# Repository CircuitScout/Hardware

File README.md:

# Hardware
Hardware of CircuitScout

- The PCBPR_Main_control_V1 is the main control board design;
- The StepperMotor_module_V2_XIAO_RP2040_w_PWR is the Coral module design;

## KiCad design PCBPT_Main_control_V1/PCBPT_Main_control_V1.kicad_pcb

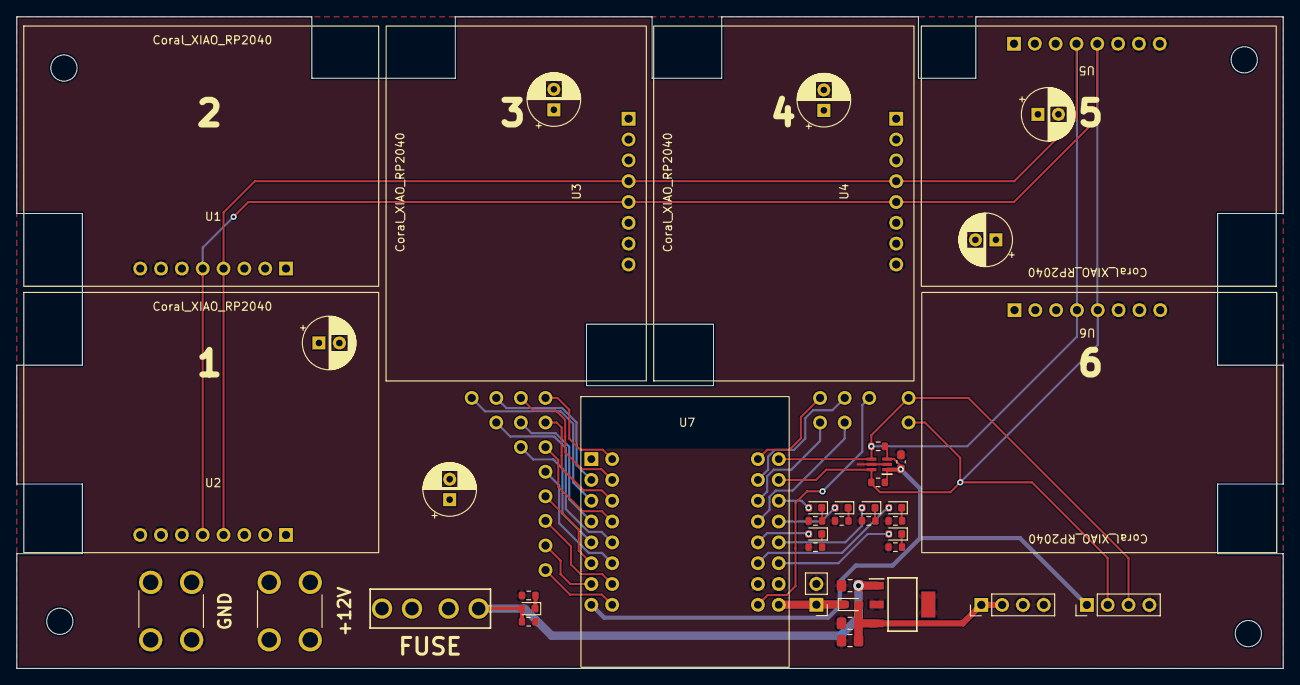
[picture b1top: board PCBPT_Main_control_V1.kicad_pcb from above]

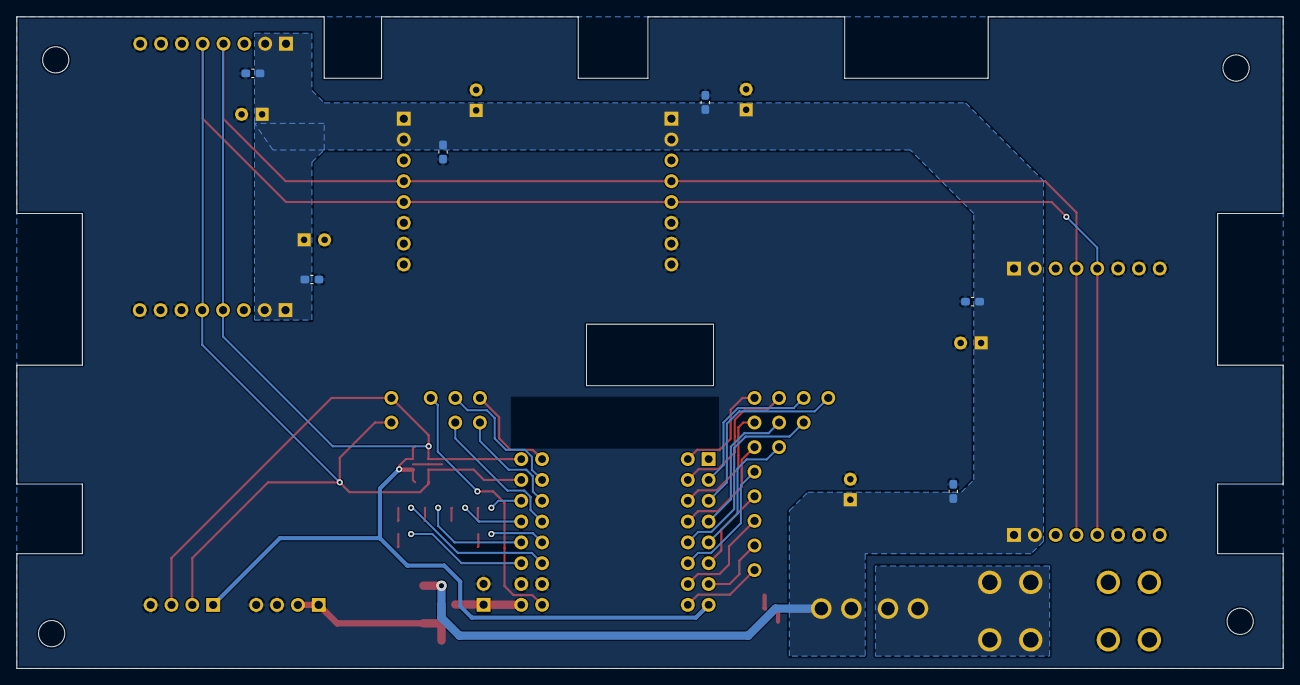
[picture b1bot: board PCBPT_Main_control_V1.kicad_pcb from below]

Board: 2 copper layers, 154.5 x 79.5 mm, 74 parts (6 on the bottom side), 40 nets.

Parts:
C1, C2, C3, C4, C5, C7: 0.1uF; C_0603_1608Metric_Pad1.08x0.95mm_HandSolder
C6: 0.01uF; C_0603_1608Metric_Pad1.08x0.95mm_HandSolder
C8, C9, C10, C11, C12, C13: 100uF; CP_Radial_D6.3mm_P2.50mm
C15: 0.47uF; C_0805_2012Metric_Pad1.18x1.45mm_HandSolder
C16: 22uF; C_0805_2012Metric_Pad1.18x1.45mm_HandSolder
C17: 0.1uF; C_0805_2012Metric_Pad1.18x1.45mm_HandSolder
D1, D2, D3, D4, D5, D6, D7: LED_Small_Filled; LED_0603_1608Metric
D8: Schottky; D_0603_1608Metric_Pad1.05x0.95mm_HandSolder
H1, H2, H3, H4: MountingHole; MountingHole_3.2mm_M3_DIN965
IC1: LM2940IMP-5.0_NOPB; SOT230P700X180-4N
IC2: LTC4311CSC6#TRPBF; SOT65P210X100-6N
J1: Fan; PinHeader_1x02_P2.54mm_Vertical
J2, J3: 8191-SEMS; 8191SEMS
J4, J8: Conn_01x04_Pin; PinHeader_1x04_P2.54mm_Vertical
R1, R2, R3, R4, R5, R6, R7, R8, R9: 10k; R_0603_1608Metric
R10: 499K; R_0603_1608Metric
TP1, TP2, TP3, TP4, TP5, TP6, TP7, TP8, TP11, TP12, TP13, TP14, TP15, TP16, TP17, TP18, TP19, TP20, TP21, TP22, TP23: TestPoint; 1_pin_sig
U1, U2, U3, U4, U5, U6: XIAO_RP2040_STEPPER_MODULE; Coral_XIAO_RP2040_stepper_ctrl
U7: Wemos/Lolin S2 mini; wemos S2 mini
U8: 3544-2

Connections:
+5V: D8.1 (K), J1.1, U7.9 (VBUS)
+12V: J2.1, J2.2, J2.3, J2.4, U8.1, U8.2
/ESP32S2_module/IND1: D2.2 (A), U7.28 (IO21)
/ESP32S2_module/IND2: D5.2 (A), U7.14 (IO35)
/ESP32S2_module/IND3: D3.2 (A), U7.13 (IO33)
/ESP32S2_module/IND4: D6.2 (A), U7.12 (IO18)
/ESP32S2_module/IND5: D4.2 (A), U7.27 (IO17)
/ESP32S2_module/IND6: D7.2 (A), U7.11 (IO16)
GND: C1.2, C2.2, C3.2, C4.2, C5.2, C6.2, C7.2, C8.2, C9.2, C10.2, C11.2, C12.2, C13.2, C15.2, C16.2, C17.2, IC1.2 (GND_1), IC1.4 (GND_2), IC2.2 (GND_1), IC2.5 (GND_2), J1.2, J3.1, J3.2, J3.3, J3.4, J4.3, J4.4, J8.4, R1.2, R2.2, R3.2, R4.2, R5.2, R6.2, R7.2, R10.1, U1.6 (GND), U1.7 (GND), U1.8 (GND), U2.6 (GND), U2.7 (GND), U2.8 (GND), U3.6 (GND), U3.7 (GND), U3.8 (GND), U4.6 (GND), U4.7 (GND), U4.8 (GND), U5.6 (GND), U5.7 (GND), U5.8 (GND), U6.6 (GND), U6.7 (GND), U6.8 (GND), U7.10 (GND), U7.26 (GND)
unnamed: D1.1 (K), R1.1
unnamed: D2.1 (K), R2.1
unnamed: D3.1 (K), R3.1
unnamed: D4.1 (K), R4.1
unnamed: D5.1 (K), R5.1
unnamed: D6.1 (K), R6.1
unnamed: D7.1 (K), R7.1
unnamed: TP1.1, U7.17 (IO1)
unnamed: TP6.1, U7.18 (IO2)
unnamed: TP11.1, U7.2 (IO3)
unnamed: TP12.1, U7.19 (IO4)
unnamed: TP16.1, U7.3 (IO5)
unnamed: TP3.1, U7.20 (IO6)
unnamed: TP5.1, U7.4 (IO7)
unnamed: TP18.1, U7.21 (IO8)
unnamed: TP17.1, U7.5 (IO9)
unnamed: TP15.1, U7.22 (IO10)
unnamed: TP13.1, U7.6 (IO11)
unnamed: TP4.1, U7.7 (IO12)
unnamed: TP2.1, U7.23 (IO13)
unnamed: TP14.1, U7.24 (IO14)
unnamed: TP19.1, U7.25 (IO15)
unnamed: TP20.1, U7.29 (IO34)
unnamed: TP22.1, U7.30 (IO36)
unnamed: TP23.1, U7.31 (IO38)
unnamed: TP21.1, U7.32 (IO40)
SCL: IC2.4 (BUS2), J8.3, R9.1, TP8.1, U1.4 (SCL), U2.4 (SCL), U3.4 (SCL), U4.4 (SCL), U5.4 (SCL), U6.4 (SCL), U7.16 (IO39)
SDA: IC2.6 (BUS1), J8.2, R8.1, TP7.1, U1.5 (SDA), U2.5 (SDA), U3.5 (SDA), U4.5 (SDA), U5.5 (SDA), U6.5 (SDA), U7.15 (IO37)
VCC: C6.1, IC2.1 (VCC), IC2.3 (ENABLE), J8.1, R8.2, R9.2, U7.8 (3V3)
VDD: C16.1, C17.1, D8.2 (A), IC1.3 (OUT), J4.1, J4.2
VPP: C1.1, C2.1, C3.1, C4.1, C5.1, C7.1, C8.1, C9.1, C10.1, C11.1, C12.1, C13.1, C15.1, D1.2 (A), IC1.1 (IN), R10.2, U1.1 (VPP), U1.2 (VPP), U2.1 (VPP), U2.2 (VPP), U3.1 (VPP), U3.2 (VPP), U4.1 (VPP), U4.2 (VPP), U5.1 (VPP), U5.2 (VPP), U6.1 (VPP), U6.2 (VPP), U8.3, U8.4

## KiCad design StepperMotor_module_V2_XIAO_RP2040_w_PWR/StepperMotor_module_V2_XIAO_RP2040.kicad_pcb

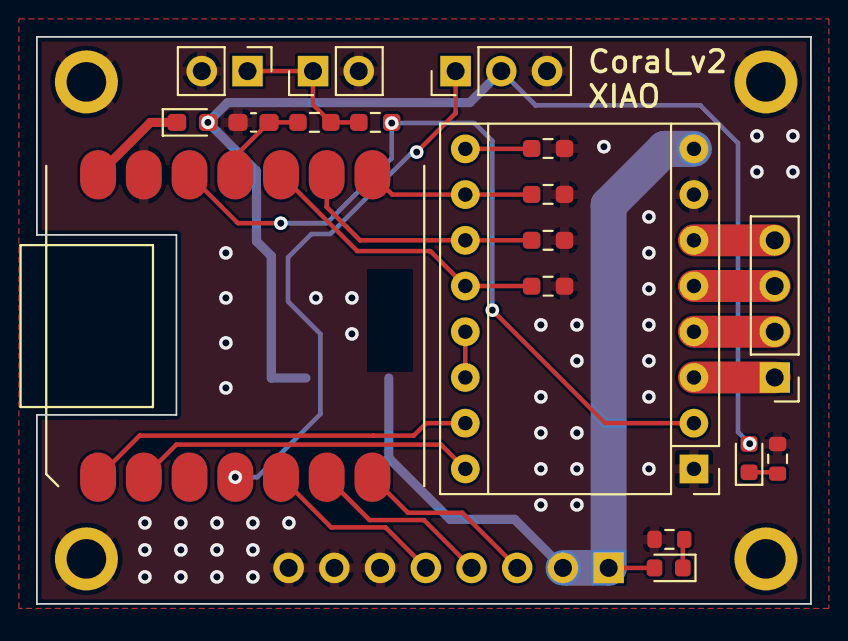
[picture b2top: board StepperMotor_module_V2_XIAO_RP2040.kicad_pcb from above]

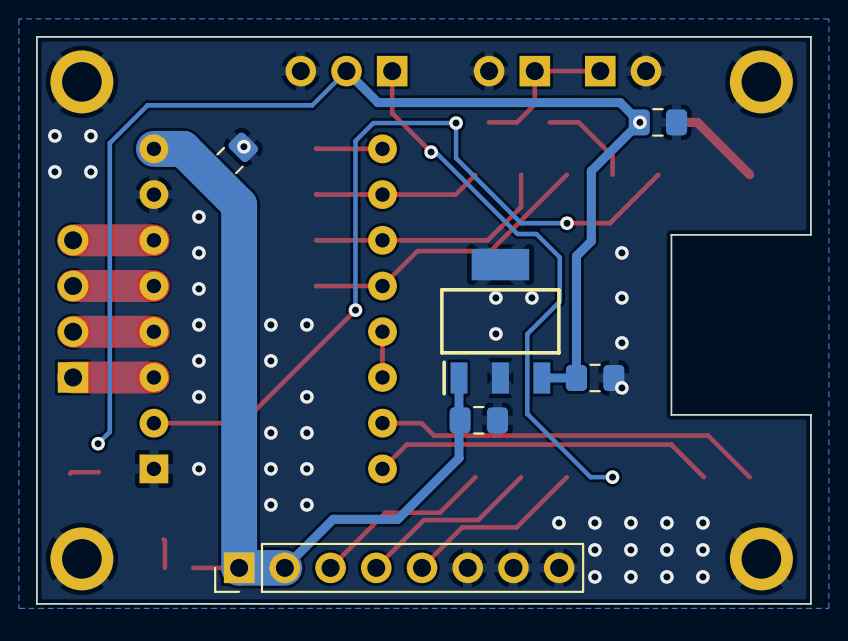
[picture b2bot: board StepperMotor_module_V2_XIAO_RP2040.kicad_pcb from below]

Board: 2 copper layers, 43.0 x 31.5 mm, 28 parts (6 on the bottom side), 24 nets.

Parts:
A1: Pololu_Breakout_A4988; Pololu_Breakout-16_15.2x20.3mm
C1, C5: 0.1uF; C_0805_2012Metric_Pad1.18x1.45mm_HandSolder
C2: 0.01uF; C_0603_1608Metric_Pad1.08x0.95mm_HandSolder
C3: 22uF; C_0805_2012Metric_Pad1.18x1.45mm_HandSolder
C4: 0.47uF; C_0805_2012Metric_Pad1.18x1.45mm_HandSolder
D1, D4: LED_Small_Filled; LED_0603_1608Metric
D2: Schottky; D_0603_1608Metric_Pad1.05x0.95mm_HandSolder
H1, H2, H3, H4: M2; MountingHole_2.2mm_M2_ISO7380_Pad
IC1: LM2940IMP-5.0_NOPB; SOT230P700X180-4N
J1: Conn_01x08_Pin; PinHeader_1x08_P2.54mm_Vertical
J3: Servo; PinHeader_1x03_P2.54mm_Vertical
J4: Limit Switch; PinHeader_1x04_P2.54mm_Vertical
J6, J7: Limit Switch; PinHeader_1x02_P2.54mm_Vertical
R1: 499K; R_0603_1608Metric_Pad0.98x0.95mm_HandSolder
R2, R3, R4, R11: 10K; R_0603_1608Metric_Pad0.98x0.95mm_HandSolder
R8, R10: 10k; R_0603_1608Metric
R12: 100; R_0603_1608Metric_Pad0.98x0.95mm_HandSolder
U1: MOUDLE-SEEEDUINO-XIAO; MOUDLE14P-SMD-2.54-21X17.8MM

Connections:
1A: A1.4 (1A), J4.2
1B: A1.3 (1B), J4.1
2A: A1.5 (2A), J4.3
2B: A1.6 (2B), J4.4
+3V3: A1.2 (VDD), R11.1, U1.12 (3V3)
/A4988_Module/M_EN: A1.9 (~ENABLE), R1.1
DIR: A1.16 (DIR), U1.2 (PA4_A1_D1)
GND: A1.1 (GND), A1.7 (GND), C1.2, C2.2, C3.2, C4.2, C5.2, H1.1, H2.1, H3.1, H4.1, IC1.2 (GND_1), IC1.4 (GND_2), J1.6, J1.7, J1.8, J3.3, J6.2, J7.2, R1.2, R2.2, R3.2, R4.2, R8.2, R10.2, U1.13 (GND)
GPIO: J1.3, U1.7 (PB08_A6_D6_TX)
LIMIT_SW_0: C2.1, R12.1, U1.11 (PA6_A10_D10_MOSI)
MS1: A1.10 (MS1), R2.1, U1.8 (PB09_A7_D7_RX)
MS2: A1.11 (MS2), R3.1, U1.9 (PA7_A8_D8_SCK)
MS3: A1.12 (MS3), R4.1, U1.10 (PA5_A9_D9_MISO)
unnamed: A1.13 (~RESET), A1.14 (~SLEEP)
unnamed: D1.1 (K), R8.1
unnamed: D2.1 (K), U1.14 (5V)
unnamed: D4.1 (K), R10.1
unnamed: J6.1, J7.1, R11.2, R12.2
PWM_S: J3.1, U1.4 (PA11_A3_D3)
SCL: J1.4, U1.6 (PA9_A5_D5_SCL)
SDA: J1.5, U1.5 (PA8_A4_D4_SDA)
STEP: A1.15 (STEP), U1.1 (PA02_A0_D0)
VCC: C3.1, C5.1, D1.2 (A), D2.2 (A), IC1.3 (OUT), J3.2
VPP: A1.8 (VMOT), C1.1, C4.1, D4.2 (A), IC1.1 (IN), J1.1, J1.2

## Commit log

2023-08-08 Migrating to new repository
2023-08-09 Adding MIT License
